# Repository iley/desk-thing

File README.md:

# The Desk Thing

Building:

```bash
mkdir -p build && cd build
cmake ..
make
```

Flashing:

```
picotool load -f -x ./build/src/desk_thing.uf2
```

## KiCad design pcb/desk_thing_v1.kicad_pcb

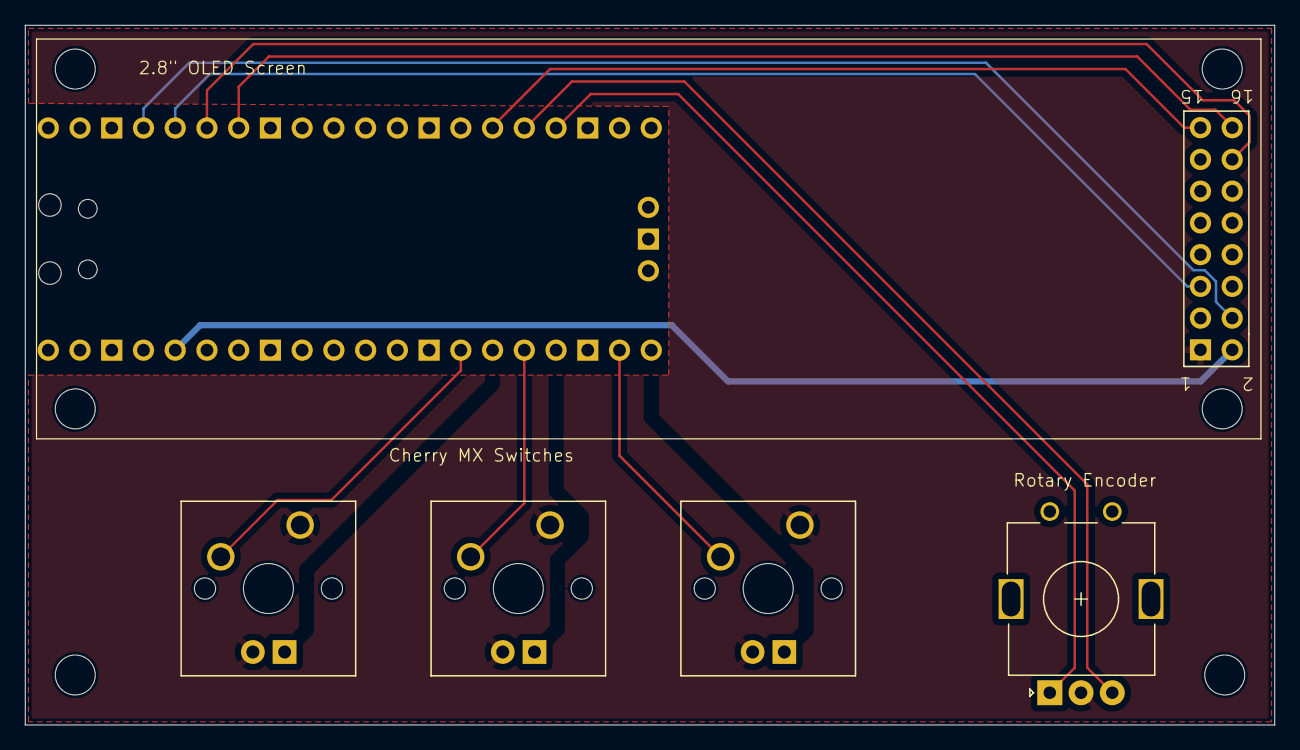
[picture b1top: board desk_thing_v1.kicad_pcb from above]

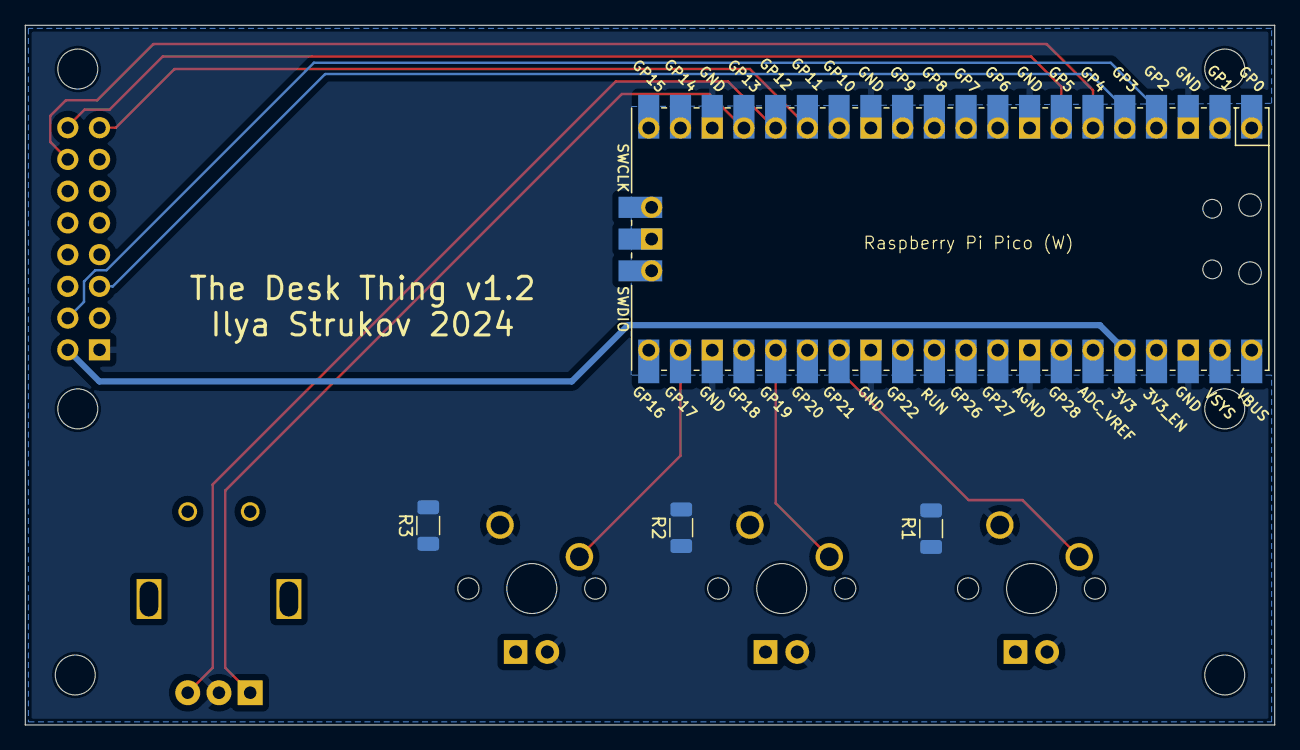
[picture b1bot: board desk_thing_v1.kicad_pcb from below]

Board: 2 copper layers, 100.0 x 56.0 mm, 9 parts (4 on the bottom side), 18 nets.

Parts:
OLED1: OLED_2_8_SSD1322
R1, R2, R3: R; R_1206_3216Metric
SW1: RotaryEncoder_Switch; RotaryEncoder_Alps_EC11E_Vertical_H20mm
SW2, SW3, SW4: SW_Push_LED; SW_Cherry_MX_1.00u_PCB
U1: Pico; RPi_Pico_SMD_TH

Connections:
+3V3: OLED1.2 (VCC), U1.36 (3V3)
/BTN1: SW2.2, U1.27 (GPIO21)
/BTN2: SW3.2, U1.25 (GPIO19)
/BTN3: SW4.2, U1.22 (GPIO17)
/LED1: R1.2, U1.26 (GPIO20)
/LED2: R2.2, U1.24 (GPIO18)
/LED3: R3.2, U1.21 (GPIO16)
/OLED_CLK: OLED1.4 (CLK), U1.4 (GPIO2)
/OLED_CS: OLED1.16 (~CS), U1.7 (GPIO5)
/OLED_DC: OLED1.14 (DC), U1.6 (GPIO4)
/OLED_MOSI: OLED1.5 (DATA), U1.5 (GPIO3)
/OLED_RESET: OLED1.15 (~RST), U1.15 (GPIO11)
/ROT_A: SW1.A, U1.17 (GPIO13)
/ROT_B: SW1.B, U1.16 (GPIO12)
GND: OLED1.1 (GND), SW1.C, SW2.1, SW2.3 (K), SW3.1, SW3.3 (K), SW4.1, SW4.3 (K), U1.3 (GND), U1.8 (GND), U1.13 (GND), U1.18 (GND), U1.23 (GND), U1.28 (GND), U1.33 (AGND), U1.38 (GND)
unnamed: R1.1, SW2.4 (A)
unnamed: R2.1, SW3.4 (A)
unnamed: R3.1, SW4.4 (A)

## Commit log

2024-07-06 PlatformIO example
2024-07-06 Add Pico SDK
2024-07-06 Add transitive dependencies
2024-07-06 Pico hello world
2024-07-06 Add u8g2
2024-07-06 (Unsuccessful) attempt to use u8g2
2024-07-06 Make the screen show something
2024-07-06 Make the basic text demo work
2024-07-06 Tweak display code
2024-07-07 Optimize the sleeps
2024-07-07 Tune SPI speed
2024-07-07 Minor code cleanup
2024-07-07 More cleanup
2024-07-13 Board design
2024-07-21 Move stuff around
2024-07-21 Working screen demo with Arduino
2024-07-31 PCB v1.1
2024-08-20 Use lower SPI rate
2024-08-20 Fix PCB mistakes
